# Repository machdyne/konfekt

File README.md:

# Konfekt Computer

Konfekt is an FPGA computer designed by Lone Dynamics Corporation.

This repo contains schematics, PCB layouts, pinouts, a 3D-printable case, example gateware and documentation.

Find more information on the [Konfekt product page](https://machdyne.com/product/konfekt-computer/).

## Programming Konfekt

Konfekt has a JTAG interface and ships with a [DFU bootloader](https://github.com/machdyne/tinydfu-bootloader) that allows the included flash [MMOD](https://machdyne.com/product/mmod) to be programmed over the USB-C port.

### DFU

The DFU bootloader is available for 5 seconds after power-on, issuing a DFU command during this period will stop the boot process until the DFU device is detached. If no command is received the boot process will continue and the user gateware will be loaded.

Install [dfu-util](http://dfu-util.sourceforge.net) (Debian/Ubuntu):

```
$ sudo apt install dfu-util
```

Update the user gateware on the flash MMOD:

```
$ sudo dfu-util -a 0 -D image.bit
```

Detach the DFU device and continue the boot process:

```
$ sudo dfu-util -a 0 -e
```

It is possible to update the bootloader itself using DFU but you shouldn't attempt this unless you have a JTAG programmer (or another method to program the MMOD) available, in case you need to restore the bootloader.

### JTAG

These examples assume you're using a "USB Blaster" JTAG cable, see the header pinout below. You will need to have [openFPGALoader](https://github.com/trabucayre/openFPGALoader) installed.

Program the configuration SRAM:

```
openFPGALoader -c usb-blaster image.bit
```

Program the flash MMOD:

```
openFPGALoader -f -c usb-blaster images/bootloader/tinydfu_konfekt.bit
```

## Blinky 

Building the blinky example requires [Yosys](https://github.com/YosysHQ/yosys), [nextpnr-ecp5](https://github.com/YosysHQ/nextpnr) and [Project Trellis](https://github.com/YosysHQ/prjtrellis).

Assuming they are installed, you can simply type `make` to build the gateware, which will be written to output/blinky.bin. You can then use [openFPGALoader](https://github.com/trabucayre/openFPGALoader) or dfu-util to write the gateware to the device.

## Linux

See the [Kakao Linux](https://github.com/machdyne/kakao) repo for the latest instructions.

### Prebuilt Images

Copy the files from the `images/linux` directory to the root directory of a FAT-formatted MicroSD card.

Konfekt ships with LiteX gateware on the user gateware section of the MMOD that is compatible with these images. After several seconds the Linux penguin should appear on the screen (HDMI) followed by a login prompt.

### Building Linux

Please follow the setup instructions in the [linux-on-litex-vexriscv](https://github.com/litex-hub/linux-on-litex-vexriscv) repo and then:

1. Build the Linux-capable gateware:

```
$ cd linux-on-litex-vexriscv
$ ./make.py --board konfekt --uart-baudrate 115200 --dcache-size 128 --icache-size 128 --build

$ ls build/konfekt
```

2. Write the gateware to the MMOD using USB DFU:

```
$ sudo dfu-util -a 0 -D build/konfekt/gateware/konfekt.bit
```

3. Copy the device tree binary `build/konfekt/konfekt.dtb` to a FAT-formatted MicroSD card.

4. Build the Linux kernel and root filesystem:

```
$ cd ..
$ git clone http://github.com/buildroot/buildroot
$ cd buildroot
$ make BR2_EXTERNAL=../linux-on-litex-vexriscv/buildroot/ litex_vexriscv_usbhost_defconfig
```

Optionally customize the kernel and buildroot packages:

```
$ make menuconfig
```

Build the kernel and rootfs:

```
$ make
$ ls output/images
```

5. Copy the `Image` and `rootfs.cpio` files from output/images to the MicroSD card.

6. Copy the OpenSBI binary (included in this repo as `konfekt/images/linux/opensbi.bin`) to the MicroSD card. Alternatively, you can build this binary by following [these instructions](https://github.com/litex-hub/linux-on-litex-vexriscv#-generating-the-opensbi-binary-optional).

7. Copy `konfekt/images/linux/boot.json` to the MicroSD card.

8. Power-cycle Konfekt. After Linux has finished booting you should see a login prompt on the HDMI display.

## LiteX

### Installing LiteX

If you haven't yet installed LiteX please see the [LiteX quick start guide](https://github.com/enjoy-digital/litex#quick-start-guide) for details on installing LiteX.

### Building Custom Gateware

Build the LiteX gateware:

```
$ cd litex-boards/litex_boards/targets
$ ./machdyne_konfekt.py --cpu-type=vexriscv --cpu-variant=lite --sys-clk-freq 40000000 --uart-baudrate 1000000 --uart-name serial --build
```

Program the LiteX gateware to SRAM over JTAG:

```
$ ./machdyne_konfekt.py --cable usb-blaster --load
```

Or program the LiteX gateware to flash over DFU:

```
$ sudo dfu-util -a 0 -D build/machdyne_konfekt/gateware/machdyne_konfekt.bit
```

## JTAG Header

The 3.3V JTAG header can be used to program the FPGA SRAM as well as the MMOD flash memory. It can also be used to provide power (5V) to the board.

```
1 2
3 4
5 6
```

| Pin | Signal |
| --- | ------ |
| 1 | TCK |
| 2 | TDI |
| 3 | TDO |
| 4 | TMS |
| 5 | 5V0 |
| 6 | GND |

## Resources

 * [fpga-dac audio player](https://github.com/machdyne/fpga-dac)

## Board Revisions

| Revision | Notes |
| -------- | ----- |
| V0 | Initial version |

## License

The contents of this repo are released under the [Lone Dynamics Open License](LICENSE.md) with the following exceptions:

- The KiCad design files contain parts of the [kicad-pmod](https://github.com/mithro/kicad-pmod) library which is released under the [Apache License, Version 2.0](https://www.apache.org/licenses/LICENSE-2.0.html).

- The KiCad design files may contain symbols and footprints released under other licenses; please contact us if we've failed to give proper attribution.

Note: You can use these designs for commercial purposes but we ask that instead of producing exact clones, that you either replace our trademarks and logos with your own or add your own next to ours.

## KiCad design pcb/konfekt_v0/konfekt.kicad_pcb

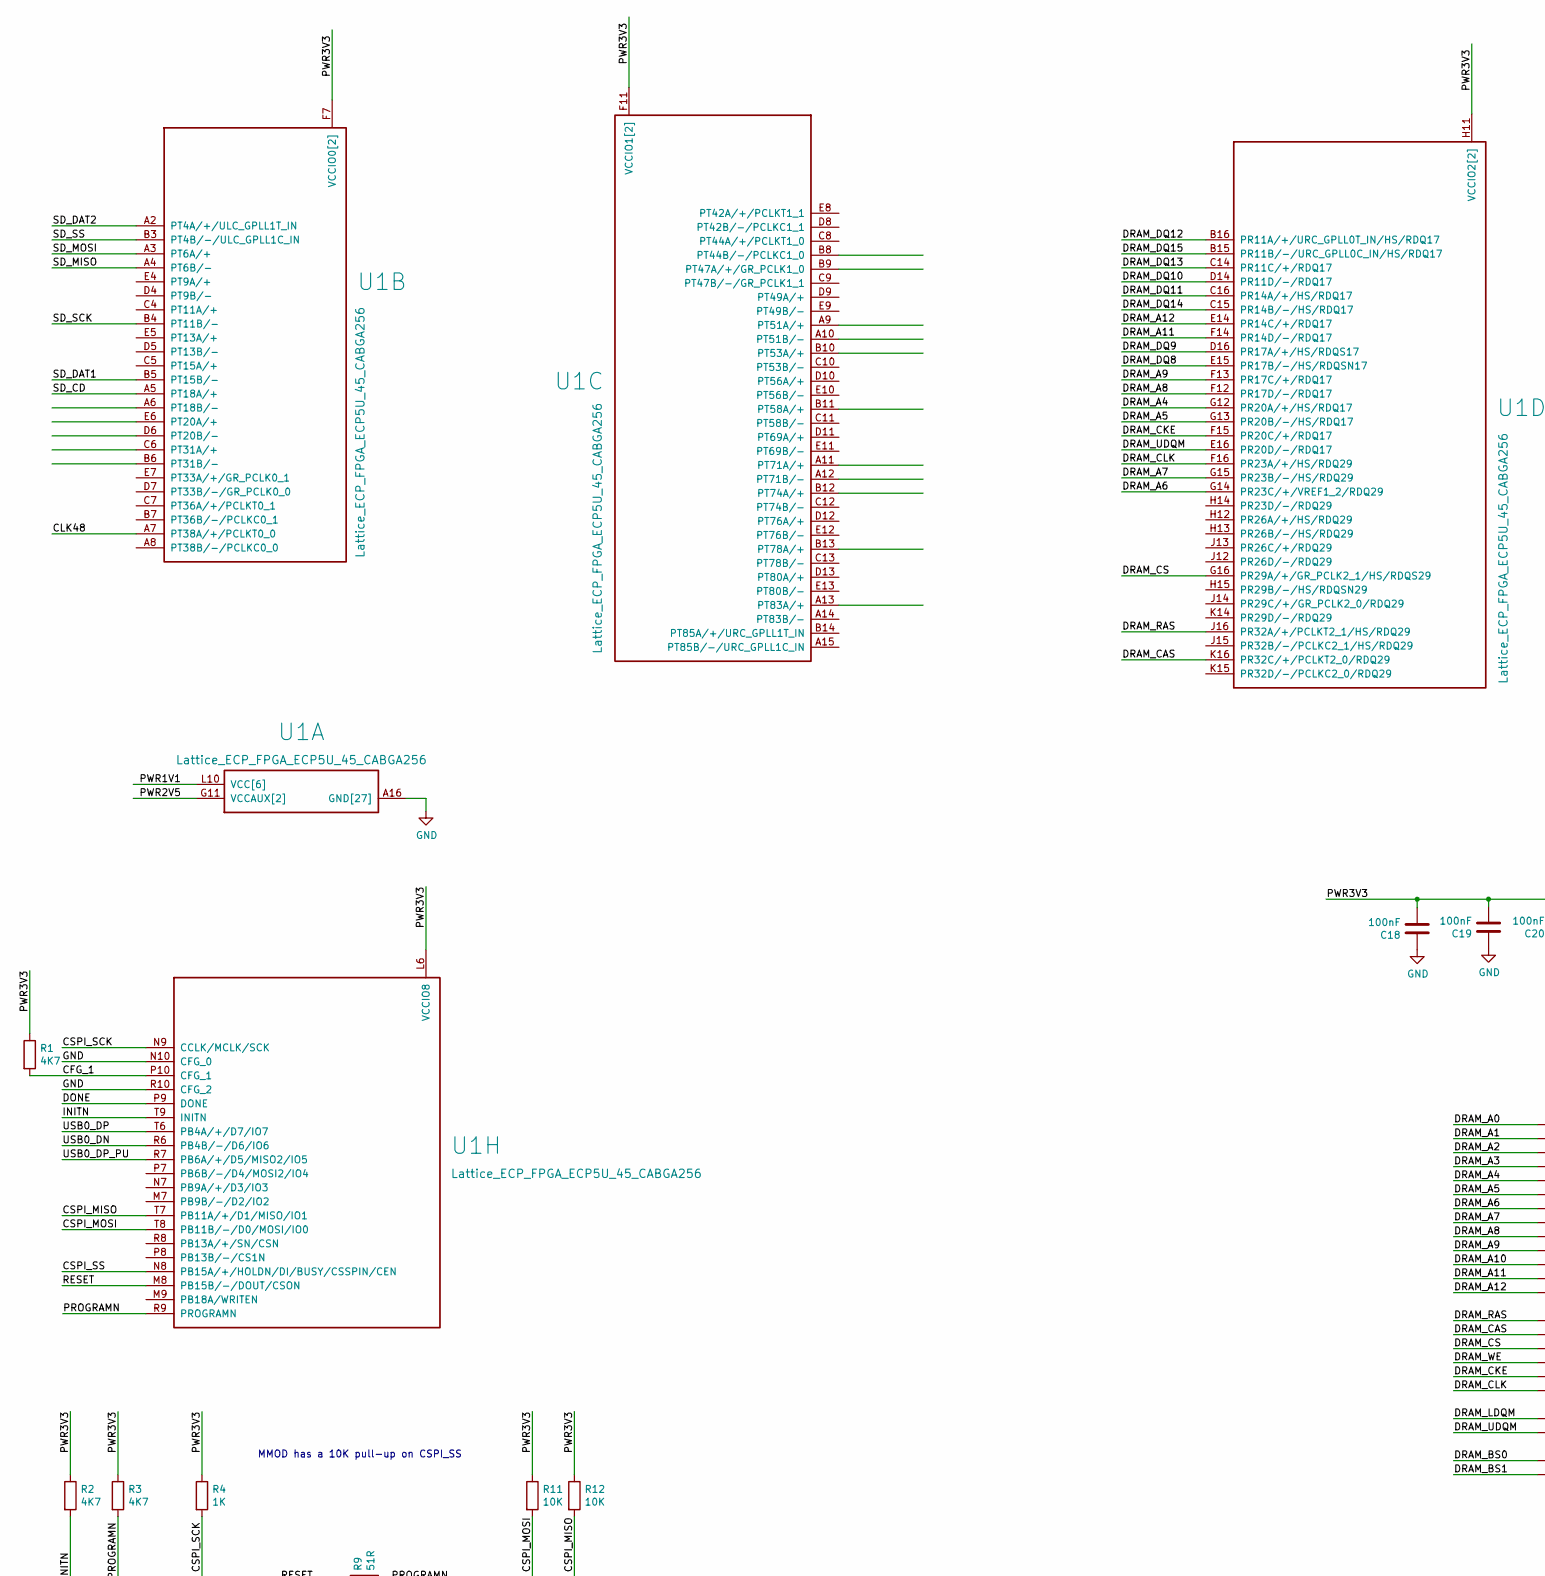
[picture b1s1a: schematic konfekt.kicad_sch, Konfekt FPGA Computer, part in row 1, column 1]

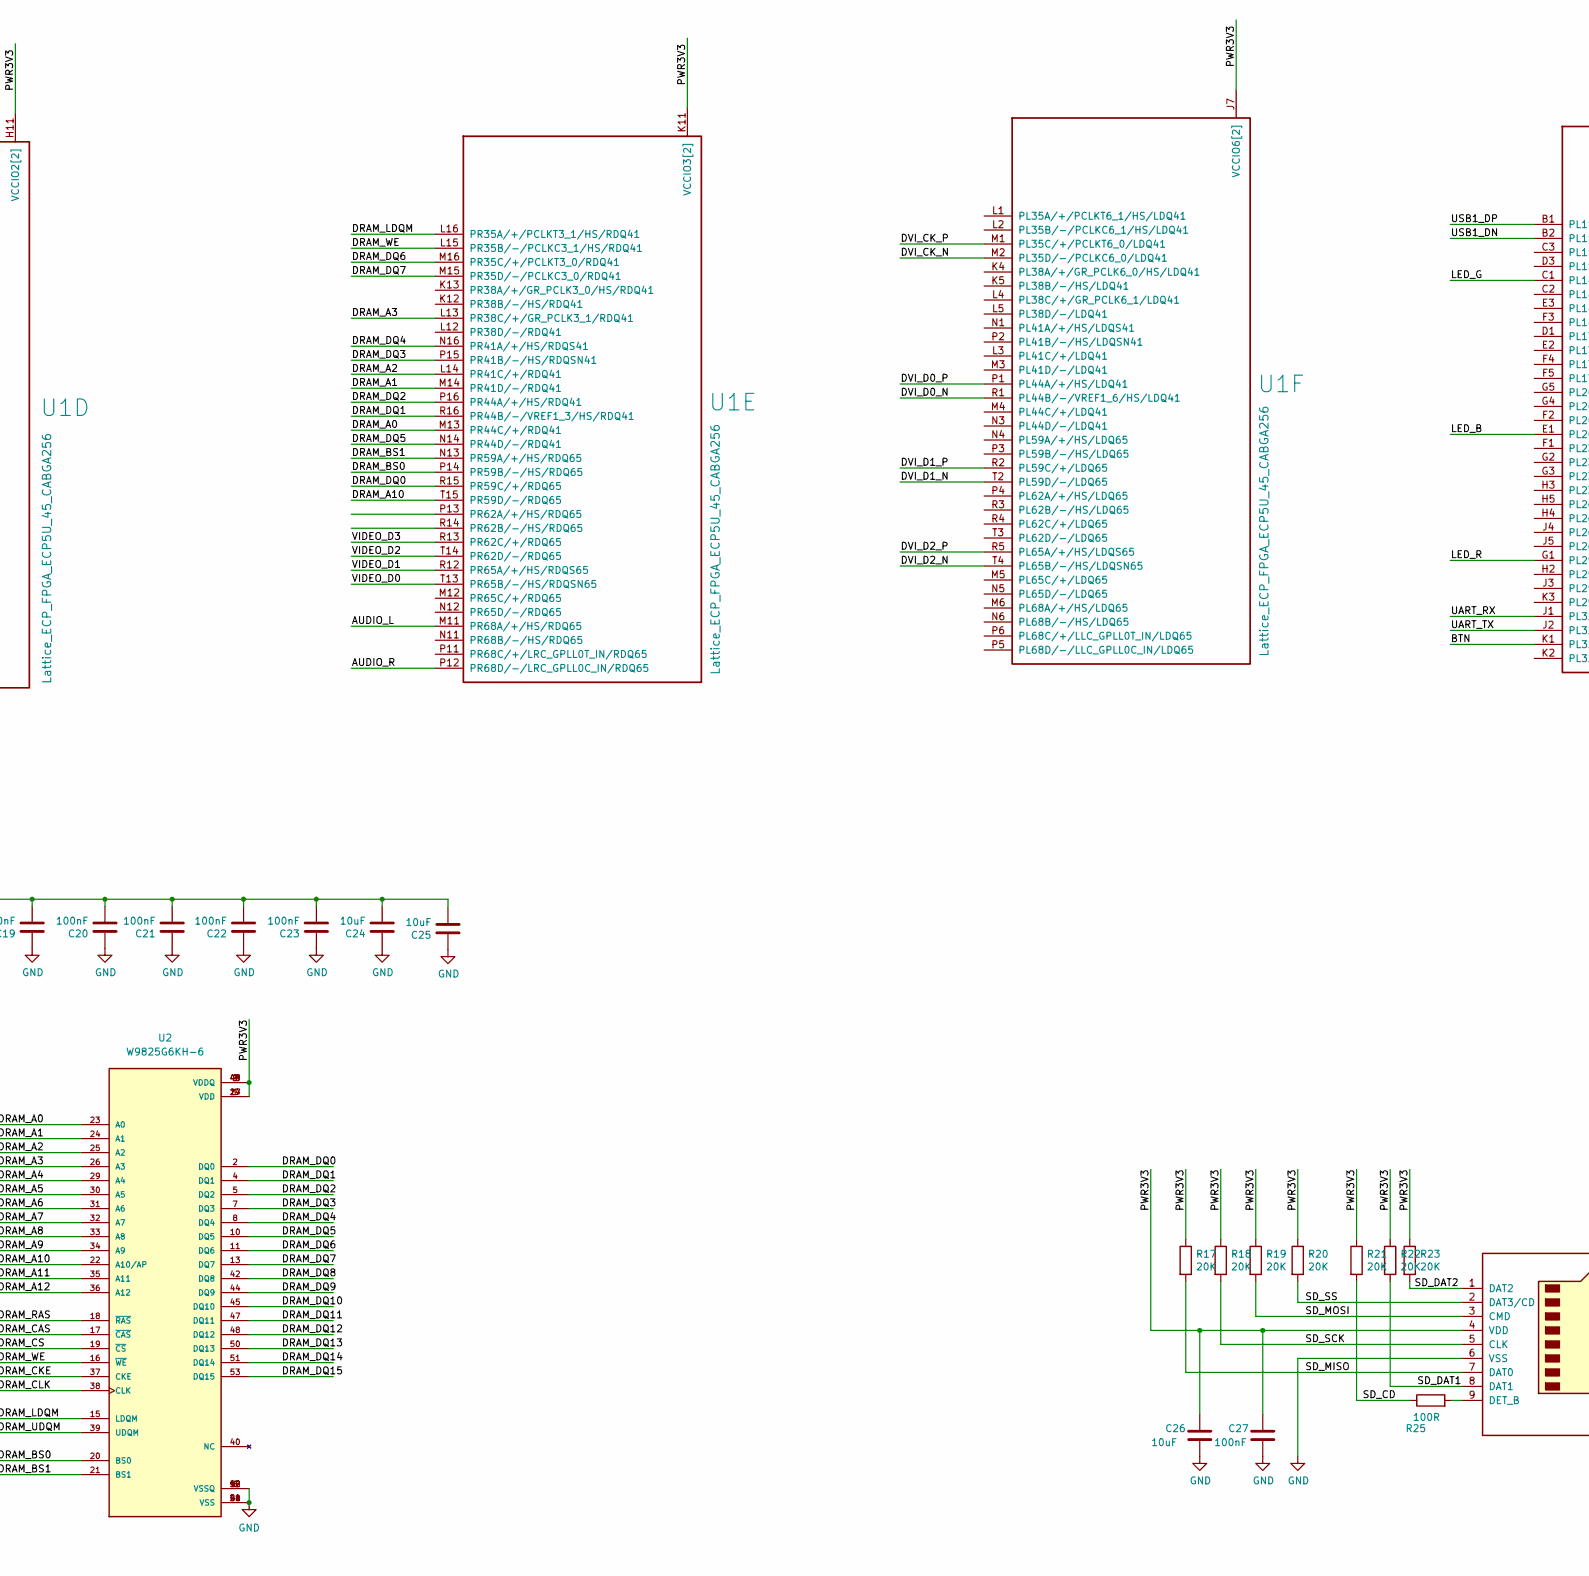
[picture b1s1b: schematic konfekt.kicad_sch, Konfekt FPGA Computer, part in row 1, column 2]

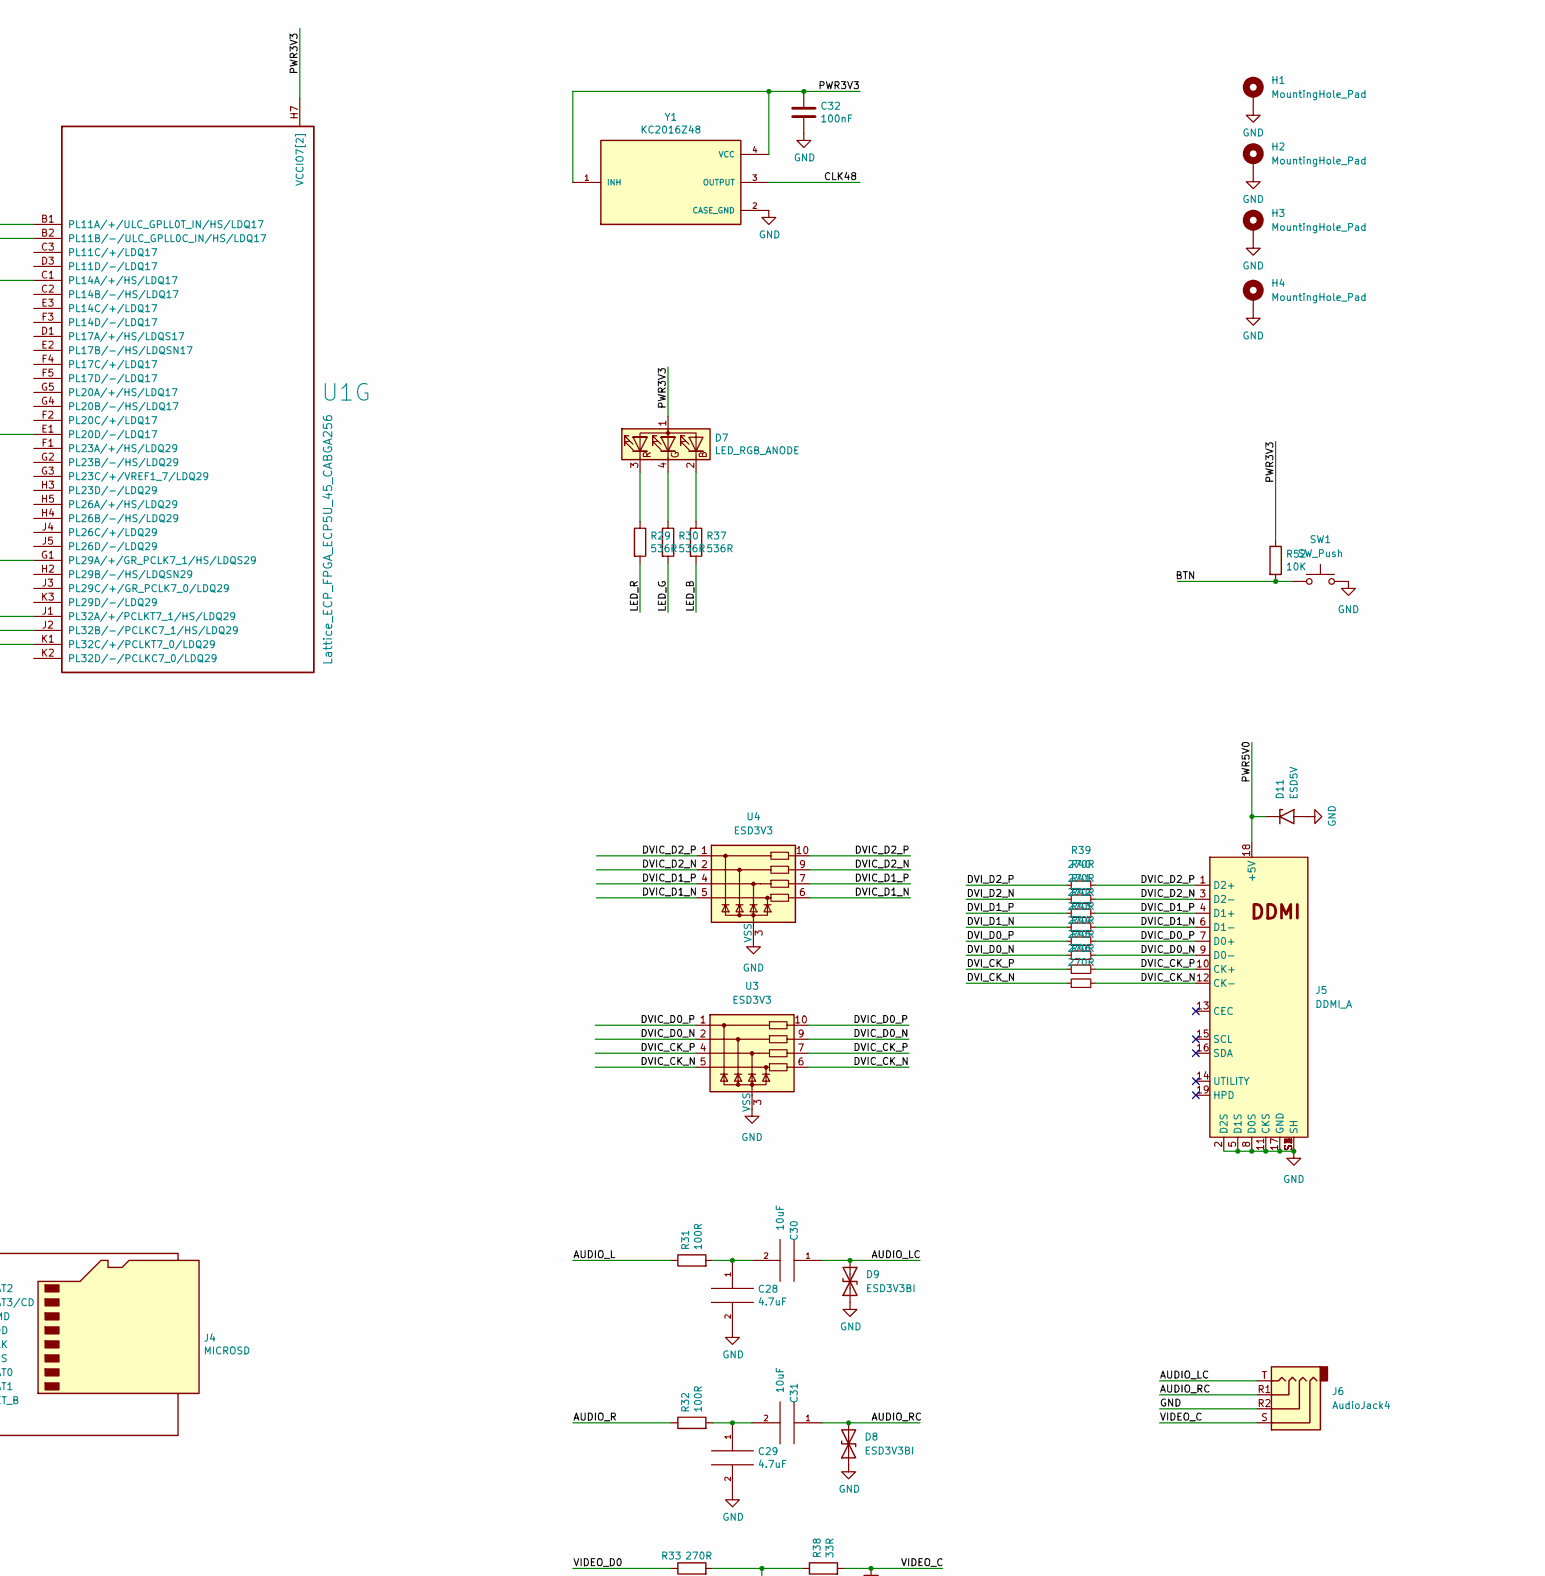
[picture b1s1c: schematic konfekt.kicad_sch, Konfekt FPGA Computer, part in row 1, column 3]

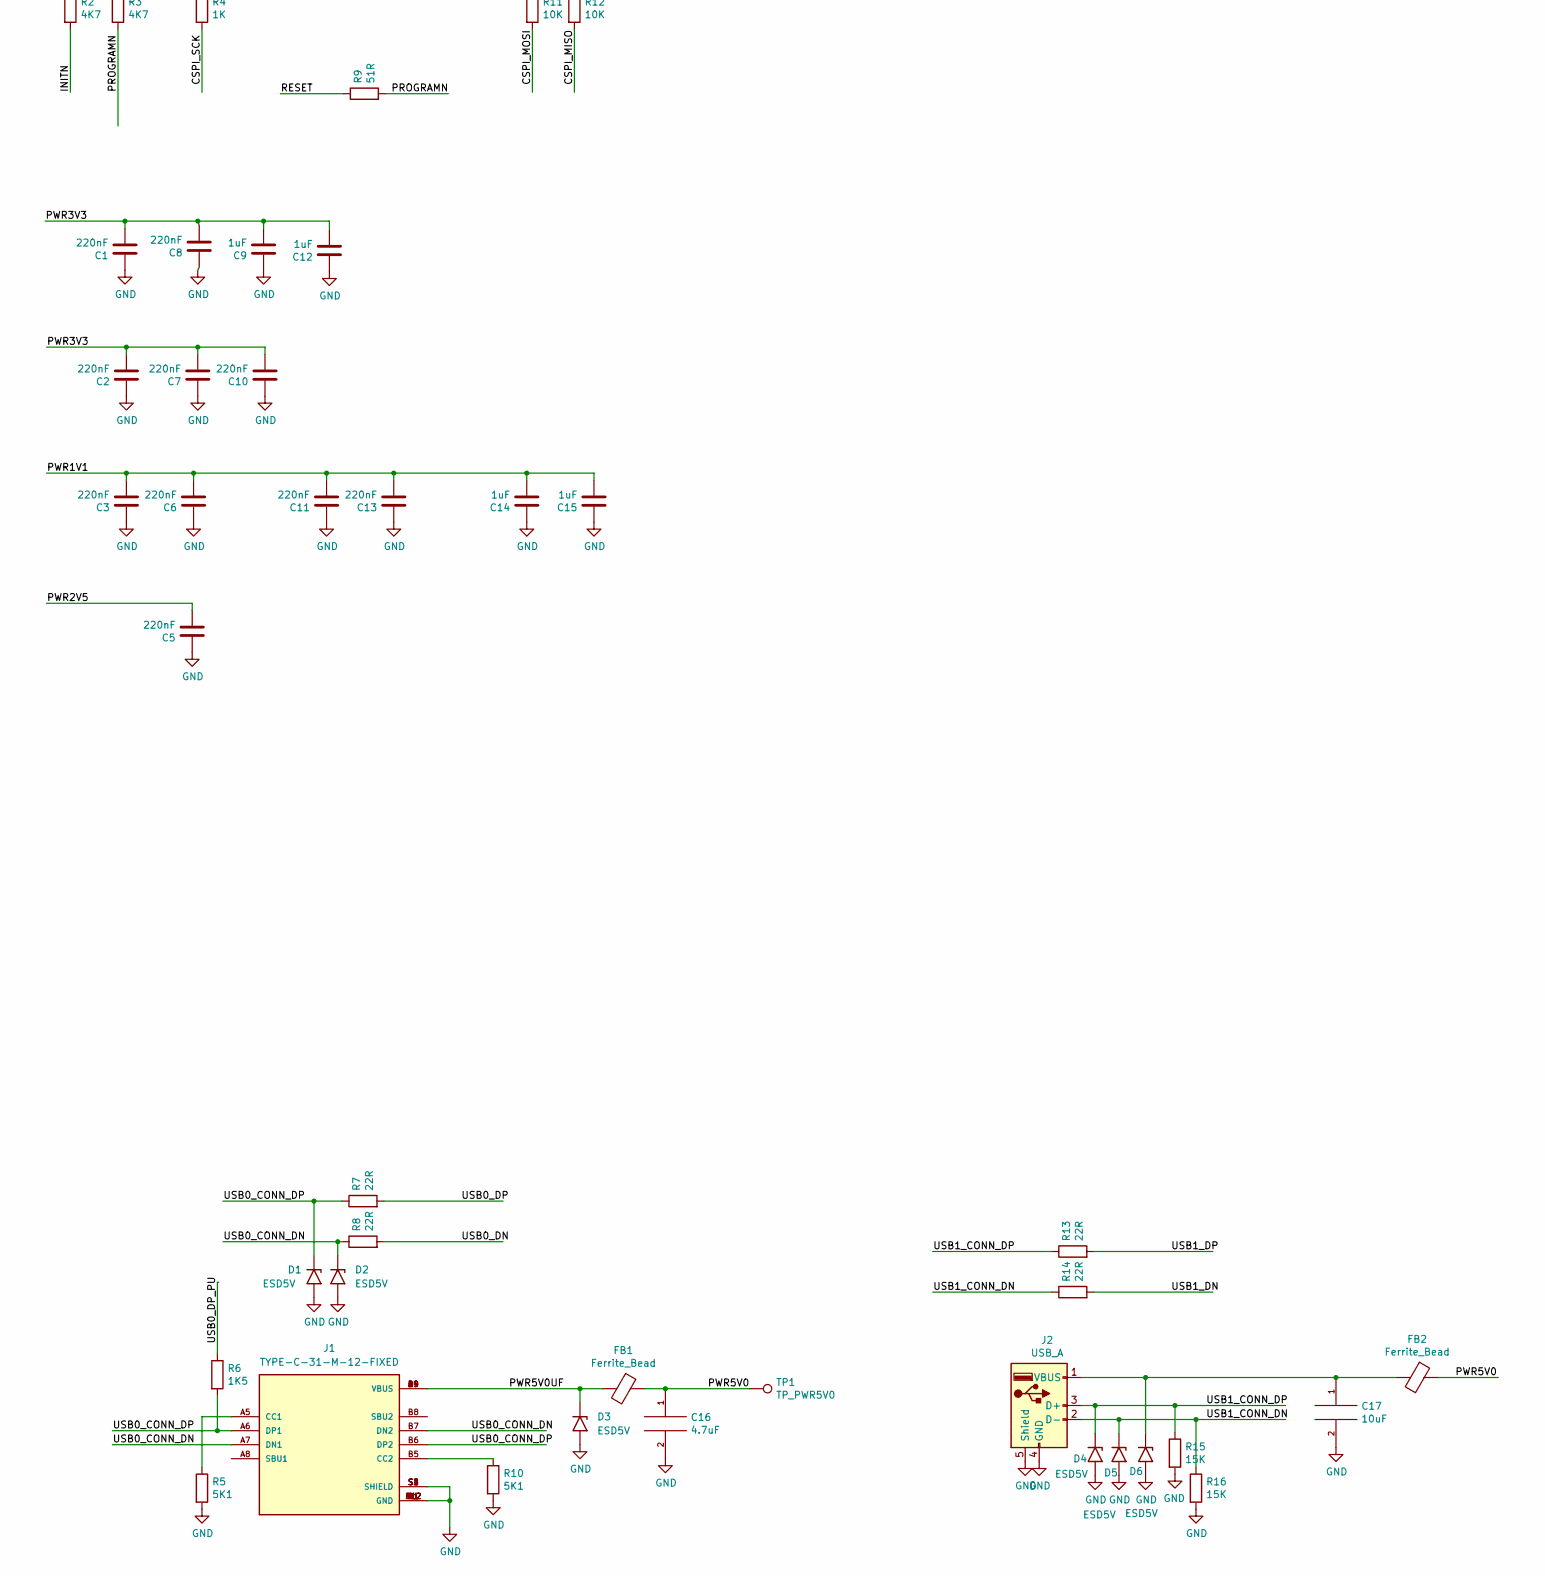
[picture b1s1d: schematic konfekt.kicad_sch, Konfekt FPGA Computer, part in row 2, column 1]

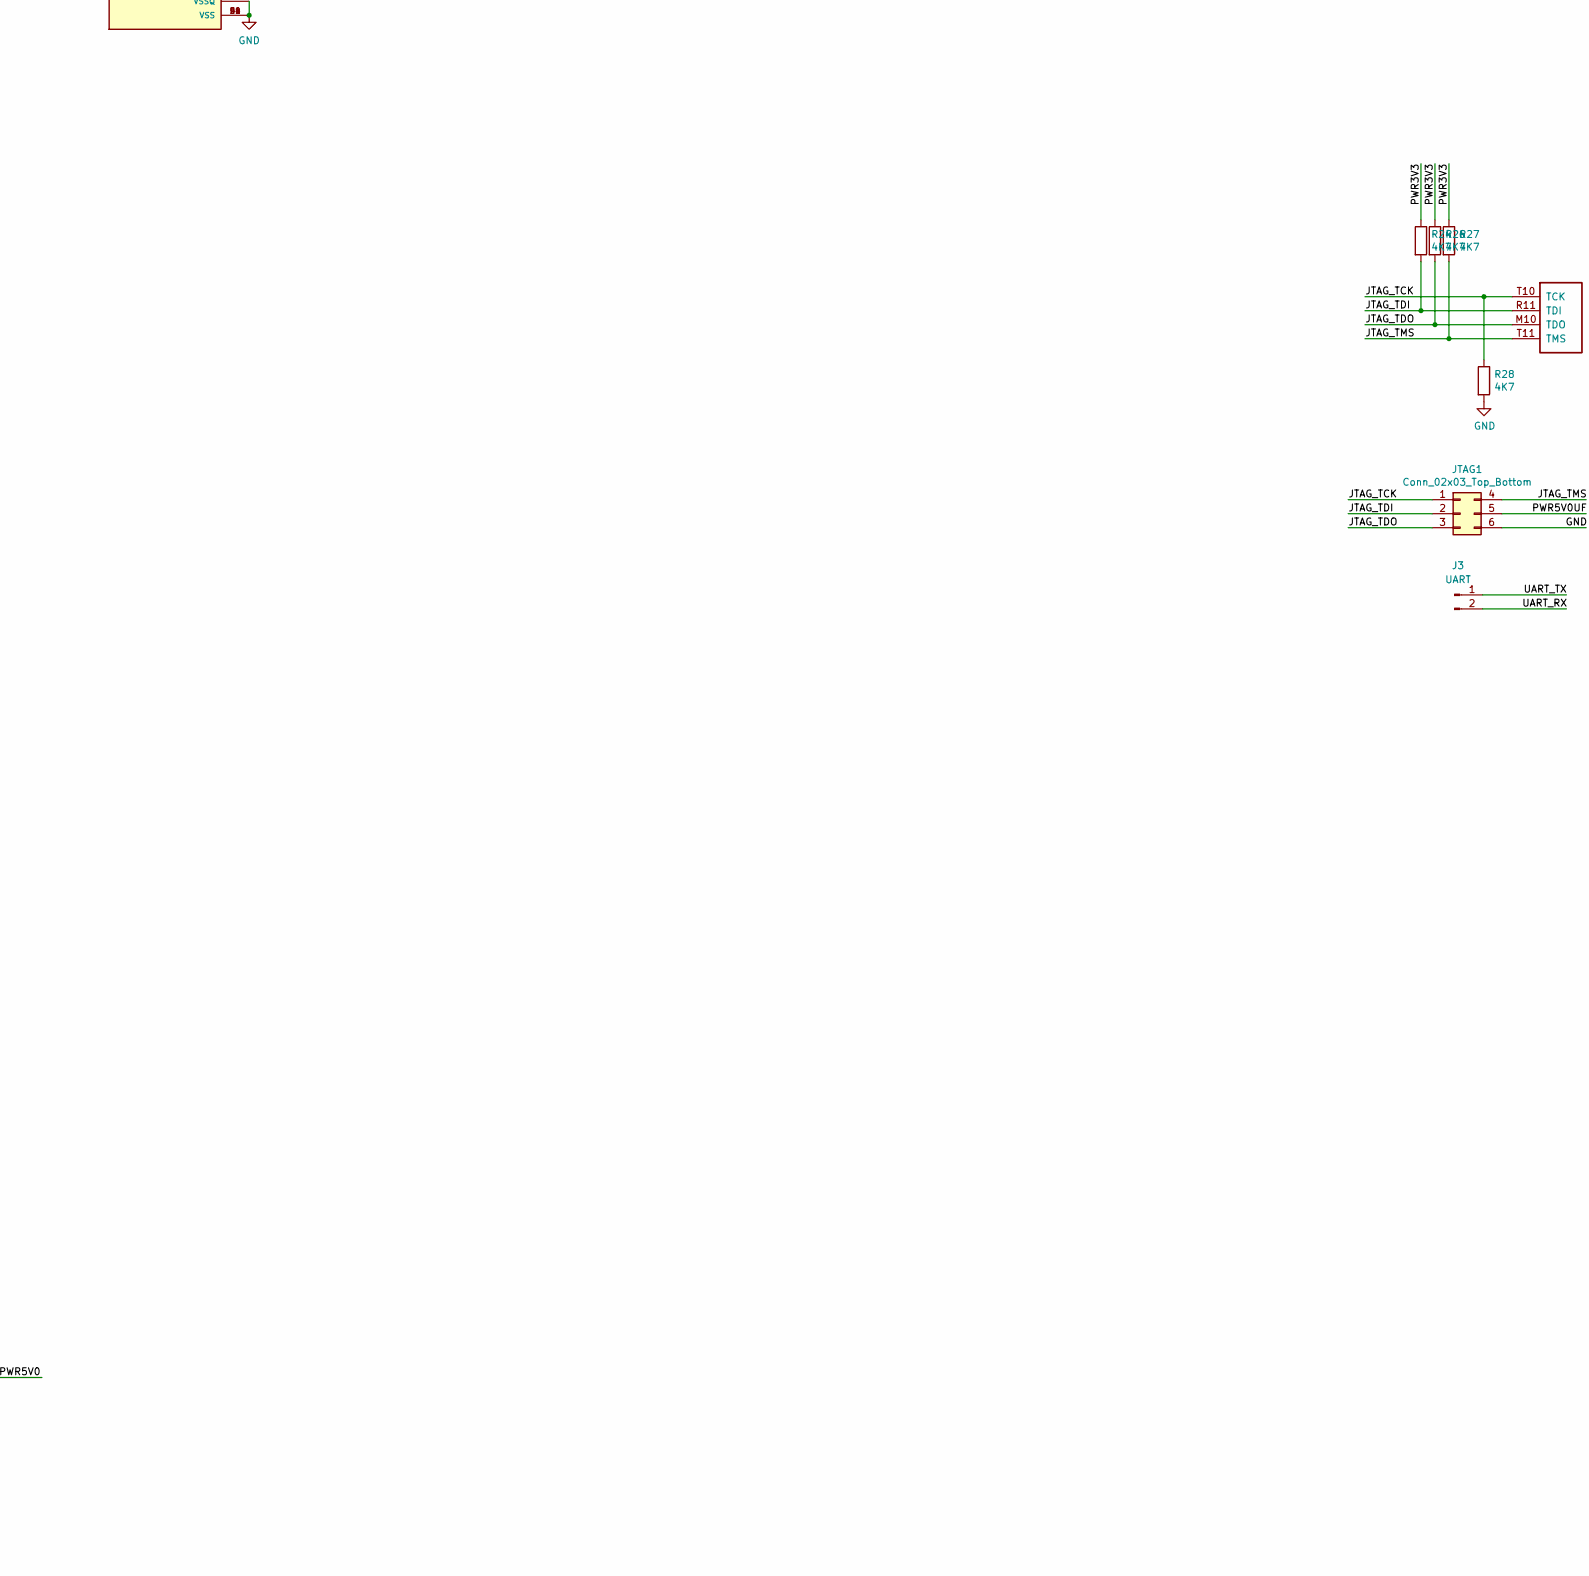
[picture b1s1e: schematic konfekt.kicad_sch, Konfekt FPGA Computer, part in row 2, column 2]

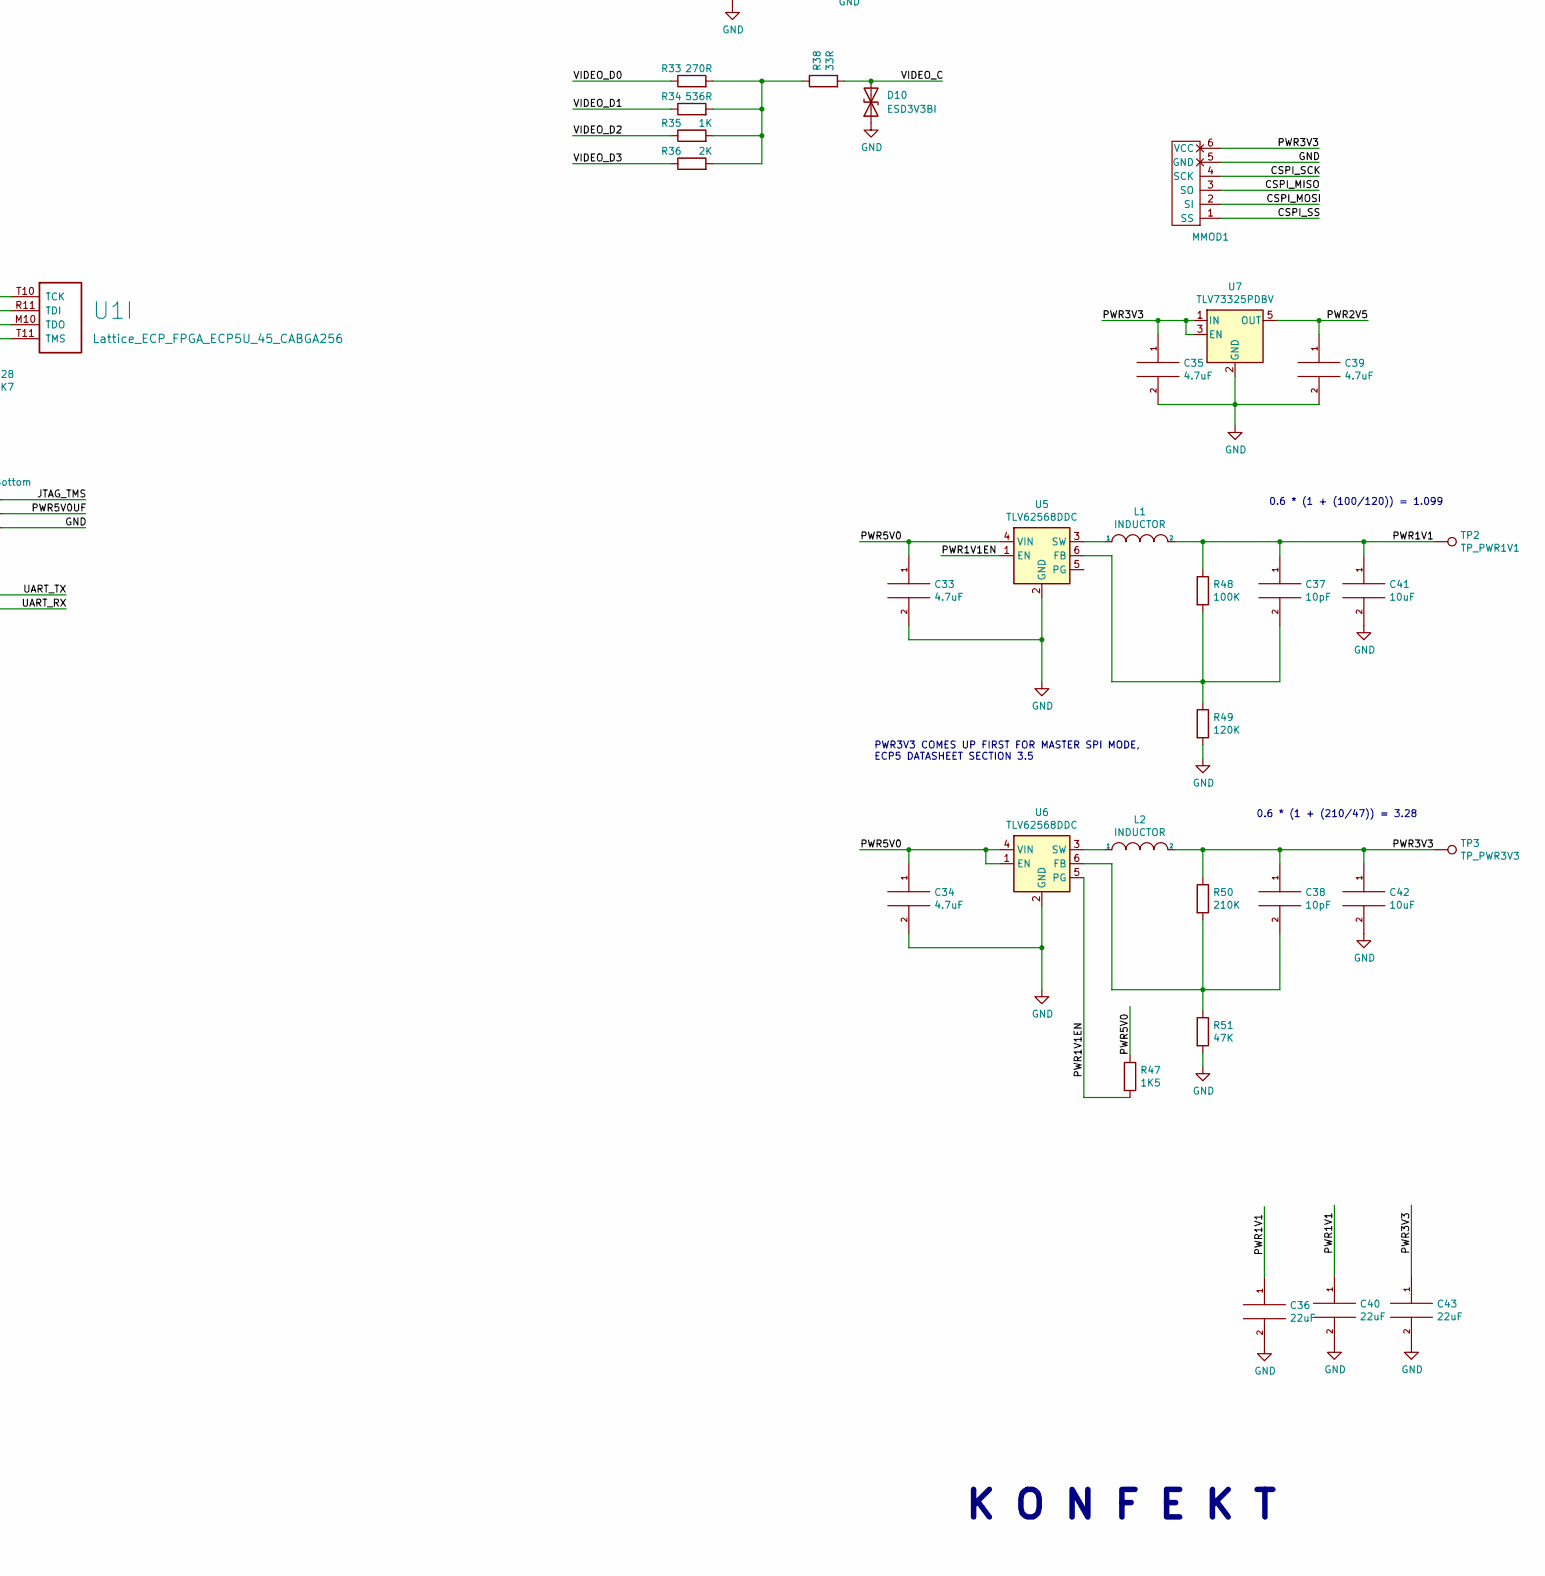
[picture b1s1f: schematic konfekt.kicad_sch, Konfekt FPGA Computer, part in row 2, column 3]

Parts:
C1, C2, C3, C5, C6, C7, C8, C10, C11, C13: 220nF; C_0603_1608Metric
C9, C12, C14, C15: 1uF; C_0603_1608Metric
C16, C28, C29, C33, C34, C35, C39: 4.7uF; C_0603_1608Metric
C17, C30, C31, C41, C42: 10uF; C_0603_1608Metric
C18, C19, C20, C21, C22, C23, C27, C32: 100nF; R_0603_1608Metric
C24, C25, C26: 10uF; R_0603_1608Metric
C36, C40, C43: 22uF; C_0603_1608Metric
C37, C38: 10pF; C_0603_1608Metric
D1, D2, D3, D4, D5, D6, D11: ESD5V; D_SOD-523
D7: LED_RGB_ANODE; LED_RGB_0606_CHANZON
D8, D9, D10: ESD3V3BI; D_SOD-523
FB1, FB2: Ferrite_Bead; R_0603_1608Metric
H1, H2, H3, H4: MountingHole_Pad; MountingHole_3.2mm_M3_Pad
J1: TYPE-C-31-M-12-FIXED; USB_C_Receptacle_HRO_TYPE-C-31-M-12-BIG-PADS; PARTREV A
J2: USB_A; USB_A_Stewart_SS-52100-001_Horizontal
J3: UART; PinHeader_1x02_P2.54mm_Vertical
J4: MICROSD; SDCARD
J5: DDMI_A; HDMI_TE_1827059-3-FIXED
J6: AudioJack4; Jack_3.5mm_PJ320D_Horizontal
JTAG1: Conn_02x03_Top_Bottom; PinHeader_2x03_P2.54mm_Vertical
L1, L2: INDUCTOR; L_0805_2012Metric
MMOD1: PMOD-Device-x1-Type-2-SPI; MMOD_Host_Socket
R1, R2, R3, R24, R26, R27, R28: 4K7; R_0603_1608Metric
R4, R35: 1K; R_0603_1608Metric
R5, R10: 5K1; R_0603_1608Metric
R6, R47: 1K5; R_0603_1608Metric
R7, R8, R13, R14: 22R; R_0603_1608Metric
R9: 51R; R_0603_1608Metric
R11, R12, R52: 10K; R_0603_1608Metric
R15, R16: 15K; R_0603_1608Metric
R17, R18, R19, R20, R21, R22, R23: 20K; R_0603_1608Metric
R25, R31, R32: 100R; R_0603_1608Metric
R29, R30, R34, R37: 536R; R_0603_1608Metric
R33: 270R; R_0603_1608Metric
R36: 2K; R_0603_1608Metric
R38: 33R; R_0603_1608Metric
R39, R40, R41, R42, R43, R44, R45, R46: 270R; R_0402_1005Metric
R48: 100K; R_0603_1608Metric
R49: 120K; R_0603_1608Metric
R50: 210K; R_0603_1608Metric
R51: 47K; R_0603_1608Metric
SW1: SW_Push; Button_2P_3x4mm
TP1: TP_PWR5V0; TestPoint_THTPad_D1.0mm_Drill0.5mm
TP2: TP_PWR1V1; TestPoint_THTPad_D1.0mm_Drill0.5mm
TP3: TP_PWR3V3; TestPoint_THTPad_D1.0mm_Drill0.5mm
U1: Lattice_ECP_FPGA_ECP5U_45_CABGA256; BGA-256_14.0x14.0mm_Layout16x16_P0.8mm_Ball0.45mm_Pad0.32mm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
U2: W9825G6KH-6; SOP80P1176X120-54N; PARTREV A05
U3, U4: ESD3V3; Diodes_UDFN-10_1.0x2.5mm_P0.5mm
U5, U6: TLV62568DDC; SOT-23-6
U7: TLV73325PDBV; SOT-23-5
Y1: KC2016Z48; OSC_KC2016Z13.5600C1KX00; PARTREV November 2020

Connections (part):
/AUDIO_L: R31.1, U1.M11 (PR68A/+/HS/RDQ65)
/AUDIO_LC: C30.1, D9.2 (A2), J6.T
/AUDIO_R: R32.1, U1.P12 (PR68D/-/LRC_GPLL0C_IN/RDQ65)
/AUDIO_RC: C31.1, D8.2 (A2), J6.R1
/BTN: R52.2, SW1.1, U1.K1 (PL32C/+/PCLKT7_0/LDQ29)
/CFG_1: R1.2, U1.P10 (CFG_1)
/CLK48: U1.A7 (PT38A/+/PCLKT0_0), Y1.3 (OUTPUT)
/CSPI_MISO: MMOD1.3 (SO), R12.2, U1.T7 (PB11A/+/D1/MISO/IO1)
/CSPI_MOSI: MMOD1.2 (SI), R11.2, U1.T8 (PB11B/-/D0/MOSI/IO0)
/CSPI_SCK: MMOD1.4 (SCK), R4.2, U1.N9 (CCLK/MCLK/SCK)
/CSPI_SS: MMOD1.1 (SS), U1.N8 (PB15A/+/HOLDN/DI/BUSY/CSSPIN/CEN)
/DONE: U1.P9 (DONE)
/DRAM_A0: U1.M13 (PR44C/+/RDQ41), U2.23 (A0)
/DRAM_A1: U1.M14 (PR41D/-/RDQ41), U2.24 (A1)
/DRAM_A2: U1.L14 (PR41C/+/RDQ41), U2.25 (A2)
/DRAM_A3: U1.L13 (PR38C/+/GR_PCLK3_1/RDQ41), U2.26 (A3)
/DRAM_A4: U1.G12 (PR20A/+/HS/RDQ17), U2.29 (A4)
/DRAM_A5: U1.G13 (PR20B/-/HS/RDQ17), U2.30 (A5)
/DRAM_A6: U1.G14 (PR23C/+/VREF1_2/RDQ29), U2.31 (A6)
/DRAM_A7: U1.G15 (PR23B/-/HS/RDQ29), U2.32 (A7)
/DRAM_A8: U1.F12 (PR17D/-/RDQ17), U2.33 (A8)
/DRAM_A9: U1.F13 (PR17C/+/RDQ17), U2.34 (A9)
/DRAM_A10: U1.T15 (PR59D/-/RDQ65), U2.22 (A10/AP)
/DRAM_A11: U1.F14 (PR14D/-/RDQ17), U2.35 (A11)
/DRAM_A12: U1.E14 (PR14C/+/RDQ17), U2.36 (A12)
/DRAM_BS0: U1.P14 (PR59B/-/HS/RDQ65), U2.20 (BS0)
/DRAM_BS1: U1.N13 (PR59A/+/HS/RDQ65), U2.21 (BS1)
/DRAM_CAS: U1.K16 (PR32C/+/PCLKT2_0/RDQ29), U2.17 (~CAS)
/DRAM_CKE: U1.F15 (PR20C/+/RDQ17), U2.37 (CKE)
/DRAM_CLK: U1.F16 (PR23A/+/HS/RDQ29), U2.38 (CLK)
/DRAM_CS: U1.G16 (PR29A/+/GR_PCLK2_1/HS/RDQS29), U2.19 (~CS)
/DRAM_DQ0: U1.R15 (PR59C/+/RDQ65), U2.2 (DQ0)
/DRAM_DQ1: U1.R16 (PR44B/-/VREF1_3/HS/RDQ41), U2.4 (DQ1)
/DRAM_DQ2: U1.P16 (PR44A/+/HS/RDQ41), U2.5 (DQ2)
/DRAM_DQ3: U1.P15 (PR41B/-/HS/RDQSN41), U2.7 (DQ3)
/DRAM_DQ4: U1.N16 (PR41A/+/HS/RDQS41), U2.8 (DQ4)
/DRAM_DQ5: U1.N14 (PR44D/-/RDQ41), U2.10 (DQ5)
/DRAM_DQ6: U1.M16 (PR35C/+/PCLKT3_0/RDQ41), U2.11 (DQ6)
/DRAM_DQ7: U1.M15 (PR35D/-/PCLKC3_0/RDQ41), U2.13 (DQ7)
/DRAM_DQ8: U1.E15 (PR17B/-/HS/RDQSN17), U2.42 (DQ8)
/DRAM_DQ9: U1.D16 (PR17A/+/HS/RDQS17), U2.44 (DQ9)
/DRAM_DQ10: U1.D14 (PR11D/-/RDQ17), U2.45 (DQ10)
/DRAM_DQ11: U1.C16 (PR14A/+/HS/RDQ17), U2.47 (DQ11)
/DRAM_DQ12: U1.B16 (PR11A/+/URC_GPLL0T_IN/HS/RDQ17), U2.48 (DQ12)
/DRAM_DQ13: U1.C14 (PR11C/+/RDQ17), U2.50 (DQ13)
/DRAM_DQ14: U1.C15 (PR14B/-/HS/RDQ17), U2.51 (DQ14)
/DRAM_DQ15: U1.B15 (PR11B/-/URC_GPLL0C_IN/HS/RDQ17), U2.53 (DQ15)
/DRAM_LDQM: U1.L16 (PR35A/+/PCLKT3_1/HS/RDQ41), U2.15 (LDQM)
/DRAM_RAS: U1.J16 (PR32A/+/PCLKT2_1/HS/RDQ29), U2.18 (~RAS)
/DRAM_UDQM: U1.E16 (PR20D/-/RDQ17), U2.39 (UDQM)
/DRAM_WE: U1.L15 (PR35B/-/PCLKC3_1/HS/RDQ41), U2.16 (~WE)
/DVIC_CK_N: J5.12 (CK-), R46.2, U3.5, U3.6
/DVIC_CK_P: J5.10 (CK+), R45.2, U3.4, U3.7
/DVIC_D0_N: J5.9 (D0-), R44.2, U3.2, U3.9
/DVIC_D0_P: J5.7 (D0+), R43.2, U3.1, U3.10
/DVIC_D1_N: J5.6 (D1-), R42.2, U4.5, U4.6
/DVIC_D1_P: J5.4 (D1+), R41.2, U4.4, U4.7
/DVIC_D2_N: J5.3 (D2-), R40.2, U4.2, U4.9
/DVIC_D2_P: J5.1 (D2+), R39.2, U4.1, U4.10
/DVI_CK_N: R46.1, U1.M2 (PL35D/-/PCLKC6_0/LDQ41)
/DVI_CK_P: R45.1, U1.M1 (PL35C/+/PCLKT6_0/LDQ41)
/DVI_D0_N: R44.1, U1.R1 (PL44B/-/VREF1_6/HS/LDQ41)
/DVI_D0_P: R43.1, U1.P1 (PL44A/+/HS/LDQ41)
/DVI_D1_N: R42.1, U1.T2 (PL59D/-/LDQ65)
/DVI_D1_P: R41.1, U1.R2 (PL59C/+/LDQ65)
/DVI_D2_N: R40.1, U1.T4 (PL65B/-/HS/LDQSN65)
/DVI_D2_P: R39.1, U1.R5 (PL65A/+/HS/LDQS65)
/INITN: R2.2, U1.T9 (INITN)
/JTAG_TCK: JTAG1.1, R28.1, U1.T10 (TCK)
/JTAG_TDI: JTAG1.2, R24.2, U1.R11 (TDI)
/JTAG_TDO: JTAG1.3, R26.2, U1.M10 (TDO)
/JTAG_TMS: JTAG1.4, R27.2, U1.T11 (TMS)
/LED_B: R37.2, U1.E1 (PL20D/-/LDQ17)
/LED_G: R30.2, U1.C1 (PL14A/+/HS/LDQ17)
/LED_R: R29.2, U1.G1 (PL29A/+/GR_PCLK7_1/HS/LDQS29)
/PROGRAMN: R3.2, R9.2, U1.R9 (PROGRAMN)
/PWR1V1: C3.2, C6.2, C11.2, C13.2, C14.2, C15.2, C36.1, C37.1, C40.1, C41.1, L1.2, R48.1, TP2.1, U1.G6 (VCC[6]), U1.G7 (VCC[6]), U1.G9 (VCC[6]), U1.L8 (VCC[6]), U1.L9 (VCC[6]), U1.L10 (VCC[6])
/PWR1V1EN: R47.2, U5.1 (EN), U6.5 (PG)
/PWR2V5: C5.2, C39.1, U1.G11 (VCCAUX[2]), U1.L7 (VCCAUX[2]), U7.5 (OUT)
/PWR3V3: C1.2, C2.2, C7.2, C8.2, C9.2, C10.2, C12.2, C18.2, C19.2, C20.2, C21.2, C22.2, C23.2, C24.2, C25.2, C26.1, C27.1, C32.1, C35.1, C38.1, C42.1, C43.1, D7.1 (A), J4.4 (VDD), L2.2, MMOD1.6 (VCC), R1.1, R2.1, R3.1, R4.1, R11.1, R12.1, R17.1, R18.1, R19.1, R20.1, R21.1, R22.1, R23.1, R24.1, R26.1, R27.1, R50.1, R52.1, TP3.1, U1.F6 (VCCIO0[2]), U1.F7 (VCCIO0[2]), U1.F10 (VCCIO1[2]), U1.F11 (VCCIO1[2]), U1.H6 (VCCIO7[2]), U1.H7 (VCCIO7[2]), U1.H11 (VCCIO2[2]), U1.J6 (VCCIO6[2]), U1.J7 (VCCIO6[2]), U1.J11 (VCCIO2[2]), U1.K11 (VCCIO3[2]), U1.L6 (VCCIO8), U1.L11 (VCCIO3[2]), U2.1 (VDD), U2.3 (VDDQ), U2.9 (VDDQ), U2.14 (VDD), U2.27 (VDD), U2.43 (VDDQ), U2.49 (VDDQ), U7.1 (IN), U7.3 (EN), Y1.1 (INH), Y1.4 (VCC)
/PWR5V0: C16.1, C33.1, C34.1, D11.1 (A1), FB1.1, FB2.1, J5.18 (+5V), R47.1, TP1.1, U5.4 (VIN), U6.1 (EN), U6.4 (VIN)
/PWR5V0UF: D3.1 (A1), FB1.2, J1.A4 (VBUS), J1.A9 (VBUS), J1.B4 (VBUS), J1.B9 (VBUS), JTAG1.5
/RESET: R9.1, U1.M8 (PB15B/-/DOUT/CSON)
/SD_CD: R21.2, R25.1, U1.A5 (PT18A/+)
/SD_DAT1: J4.8 (DAT1), R22.2, U1.B5 (PT15B/-)
/SD_DAT2: J4.1 (DAT2), R23.2, U1.A2 (PT4A/+/ULC_GPLL1T_IN)
/SD_MISO: J4.7 (DAT0), R17.2, U1.A4 (PT6B/-)
/SD_MOSI: J4.3 (CMD), R19.2, U1.A3 (PT6A/+)
/SD_SCK: J4.5 (CLK), R18.2, U1.B4 (PT11B/-)
/SD_SS: J4.2 (DAT3/CD), R20.2, U1.B3 (PT4B/-/ULC_GPLL1C_IN)
/UART_RX: J3.2, U1.J1 (PL32A/+/PCLKT7_1/HS/LDQ29)
/UART_TX: J3.1, U1.J2 (PL32B/-/PCLKC7_1/HS/LDQ29)
/USB0_CONN_DN: D2.1 (A1), J1.A7 (DN1), J1.B7 (DN2), R8.1
/USB0_CONN_DP: D1.1 (A1), J1.A6 (DP1), J1.B6 (DP2), R6.2, R7.1
/USB0_DN: R8.2, U1.R6 (PB4B/-/D6/IO6)
/USB0_DP: R7.2, U1.T6 (PB4A/+/D7/IO7)
/USB0_DP_PU: R6.1, U1.R7 (PB6A/+/D5/MISO2/IO5)
/USB1_CONN_DN: D5.1 (A1), J2.2 (D-), R14.1, R16.1
/USB1_CONN_DP: D4.1 (A1), J2.3 (D+), R13.1, R15.1
/USB1_DN: R14.2, U1.B2 (PL11B/-/ULC_GPLL0C_IN/HS/LDQ17)
/USB1_DP: R13.2, U1.B1 (PL11A/+/ULC_GPLL0T_IN/HS/LDQ17)
/VIDEO_C: D10.2 (A2), J6.S, R38.2
/VIDEO_D0: R33.1, U1.T13 (PR65B/-/HS/RDQSN65)
/VIDEO_D1: R34.1, U1.R12 (PR65A/+/HS/RDQS65)
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
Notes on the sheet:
K O N F E K T
PWR3V3 COMES UP FIRST FOR MASTER SPI MODE, ECP5 DATASHEET SECTION 3.5
0.6 * (1 + (210/47)) = 3.28
MMOD has a 10K pull-up on CSPI_SS
0.6 * (1 + (100/120)) = 1.099

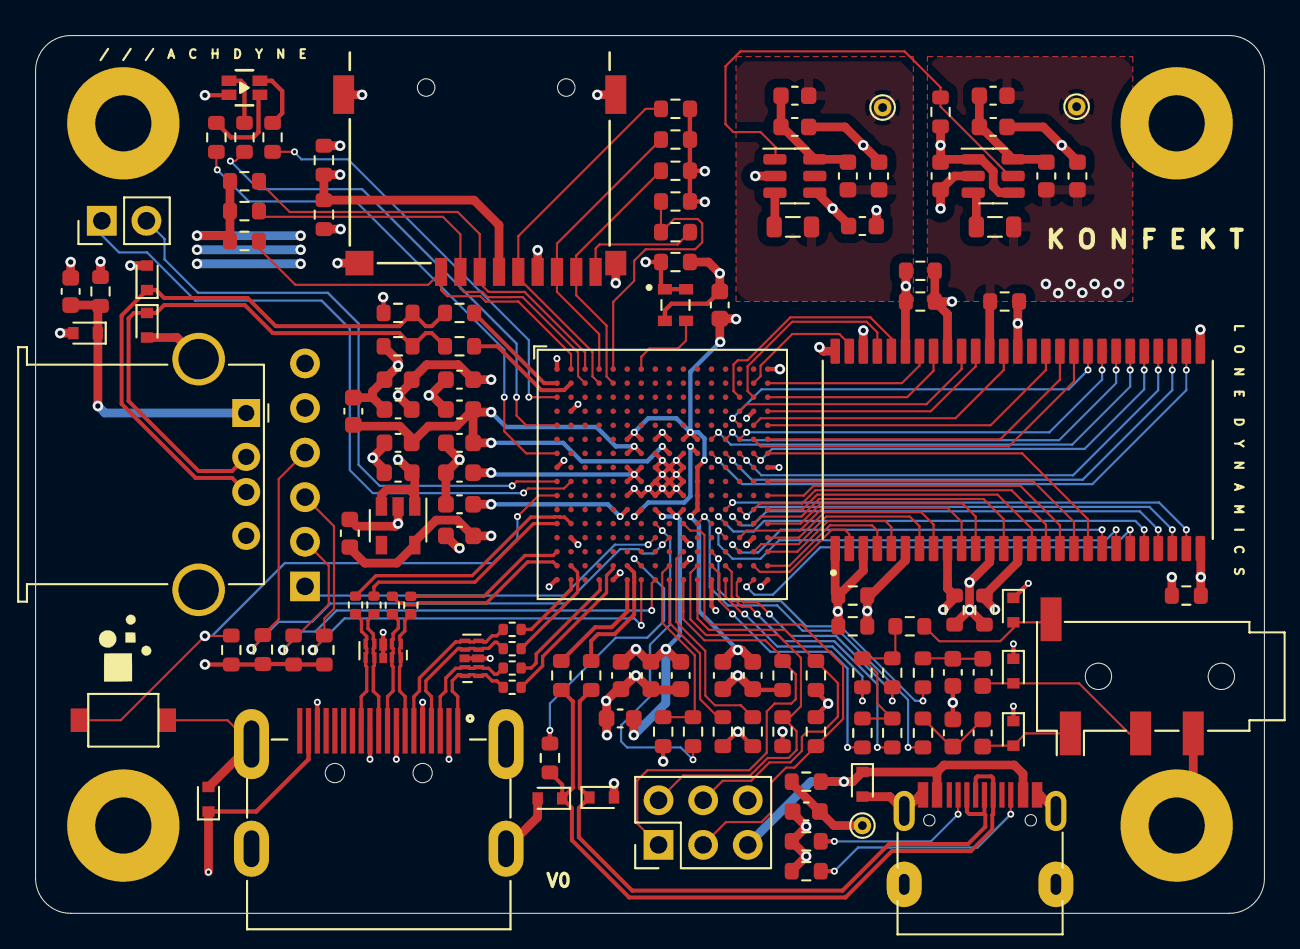
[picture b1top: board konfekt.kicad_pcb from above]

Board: 4 copper layers, 70.0 x 50.0 mm, 133 parts (1 on the bottom side), 120 nets.

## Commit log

2022-12-27 add image
2023-01-20 increase height, add hardware notes
2023-02-05 complete lpf
2023-02-09 fix lpf
2023-02-09 add usb device to lpf
2023-05-06 add pcb
2023-05-06 hide footprint text

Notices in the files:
pcb/konfekt_v0/konfekt.kicad_sch:
Copyright © 2022 Lone Dynamics Corporation
